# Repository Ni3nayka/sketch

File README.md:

# sketch
This repository contains small programs for different robots

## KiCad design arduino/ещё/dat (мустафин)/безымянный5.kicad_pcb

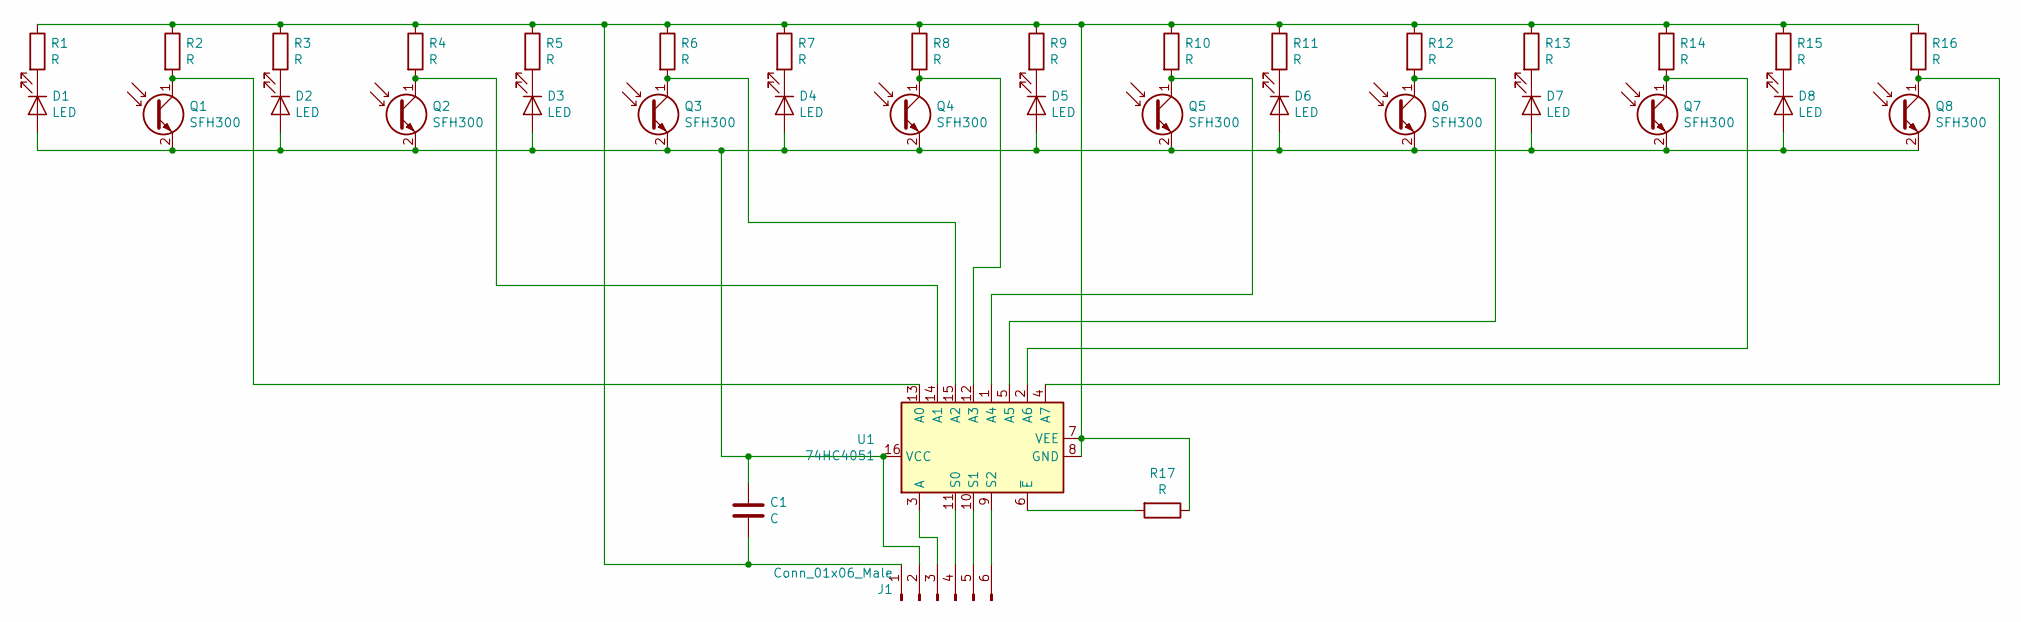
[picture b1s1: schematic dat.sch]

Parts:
C1: C; C_0805_2012Metric_Pad1.15x1.40mm_HandSolder
D1, D2, D3, D4, D5, D6, D7, D8: LED; LED_0805_2012Metric_Castellated
J1: Conn_01x06_Male; PinHeader_1x06_P2.54mm_Vertical
Q1, Q2, Q3, Q4, Q5, Q6, Q7, Q8: SFH300; LED_D5.0mm_Clear
R1, R2, R3, R4, R5, R6, R7, R8, R9, R10, R11, R12, R13, R14, R15, R16, R17: R; R_0805_2012Metric_Pad1.15x1.40mm_HandSolder
U1: 74HC4051; SOP-16_4.55x10.3mm_P1.27mm

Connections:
unnamed: C1.1, D1.2 (A), D2.2 (A), D3.2 (A), D4.2 (A), D5.2 (A), D6.2 (A), D7.2 (A), D8.2 (A), J1.2, Q1.2 (E), Q2.2 (E), Q3.2 (E), Q4.2 (E), Q5.2 (E), Q6.2 (E), Q7.2 (E), Q8.2 (E), U1.16 (VCC)
unnamed: C1.2, J1.1, R1.1, R2.1, R3.1, R4.1, R5.1, R6.1, R7.1, R8.1, R9.1, R10.1, R11.1, R12.1, R13.1, R14.1, R15.1, R16.1, R17.1, U1.7 (VEE), U1.8 (GND)
unnamed: D1.1 (K), R1.2
unnamed: D2.1 (K), R3.2
unnamed: D3.1 (K), R5.2
unnamed: D4.1 (K), R7.2
unnamed: D5.1 (K), R9.2
unnamed: D6.1 (K), R11.2
unnamed: D7.1 (K), R13.2
unnamed: D8.1 (K), R15.2
unnamed: J1.3, U1.3 (A)
unnamed: J1.4, U1.11 (S0)
unnamed: J1.5, U1.10 (S1)
unnamed: J1.6, U1.9 (S2)
unnamed: Q1.1 (C), R2.2, U1.13 (A0)
unnamed: Q2.1 (C), R4.2, U1.14 (A1)
unnamed: Q3.1 (C), R6.2, U1.15 (A2)
unnamed: Q4.1 (C), R8.2, U1.12 (A3)
unnamed: Q5.1 (C), R10.2, U1.1 (A4)
unnamed: Q6.1 (C), R12.2, U1.5 (A5)
unnamed: Q7.1 (C), R14.2, U1.2 (A6)
unnamed: Q8.1 (C), R16.2, U1.4 (A7)
unnamed: R17.2, U1.6 (~E)

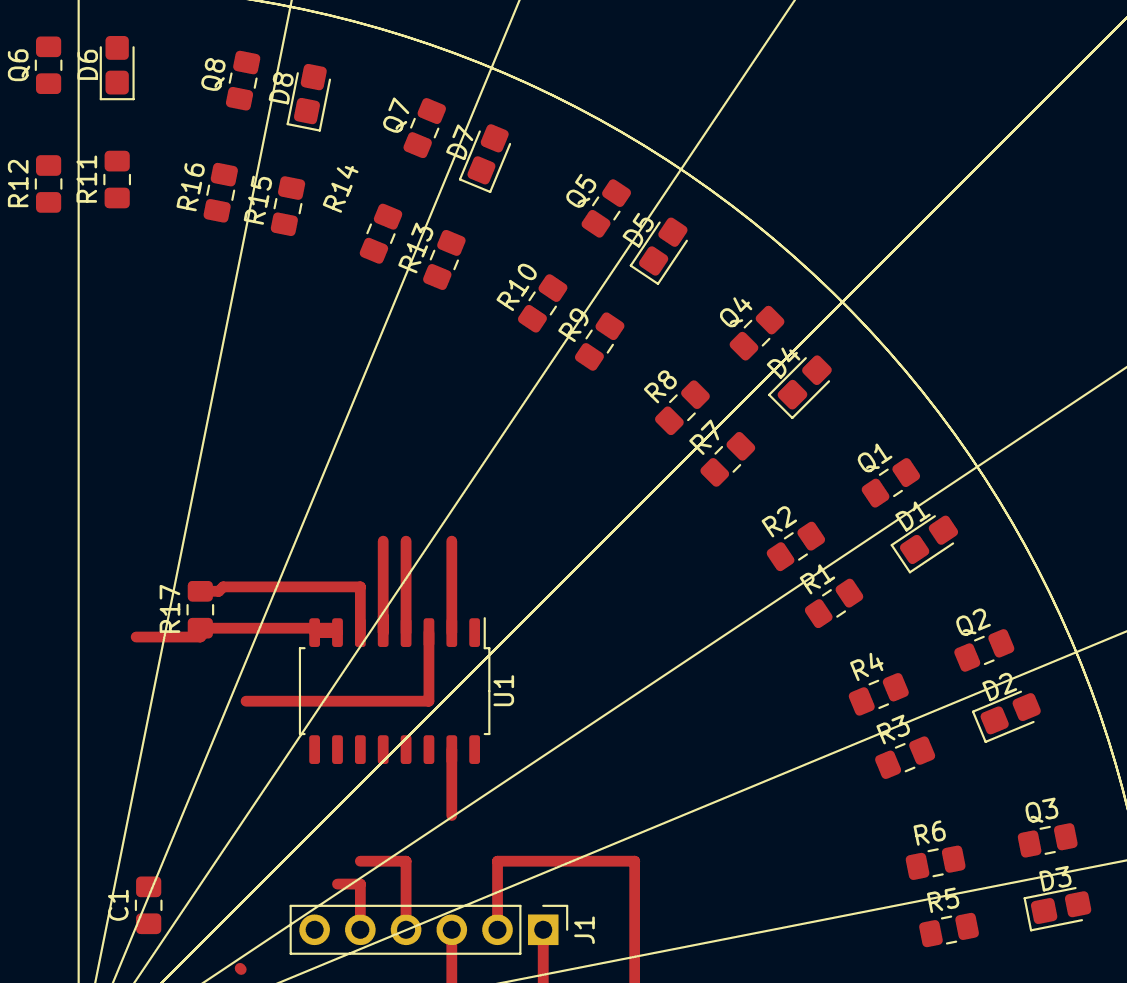
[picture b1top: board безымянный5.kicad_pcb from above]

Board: 2 copper layers, 36 parts (0 on the bottom side), 23 nets.

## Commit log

2021-01-06 first download
2021-01-06 update library
2021-02-01 add info for c++
2021-03-05 add dynamic coding
2021-05-12 add CM shema
2021-05-13 add CM
2021-07-14 add 3D
2021-09-14 add informathic_laba
2021-09-25 add roborace
2021-09-28 class work
2021-09-28 update informatic lesson
2021-10-02 informatica
2021-10-03 folder
2021-10-05 add class informatic
2021-10-11 add work
2022-03-15 add NTI
2022-07-03 packet
2022-08-08 add server runner code
2022-09-07 add robofinist
2022-10-09 add trackduino
2022-10-22 first test processing
2023-01-03 PID test
2023-02-03 add old shemes
2023-03-26 add sprint-layout shemes
2023-03-26 domofon key
2023-06-08 add ralli code
2023-11-02 voltmetr_SD
2024-01-26 start learn Dart
2024-01-26 first Dart project
2024-03-10 radio 433 test
2024-07-20 add project star-potolok
